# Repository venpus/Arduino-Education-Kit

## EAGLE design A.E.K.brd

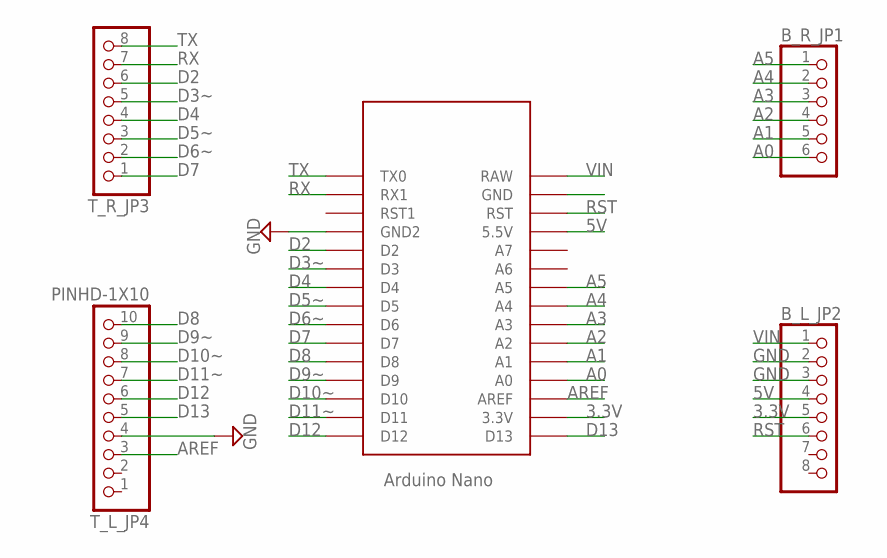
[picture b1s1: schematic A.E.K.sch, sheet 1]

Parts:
B_L_JP2: PINHD-1X8BIG; 1X08-BIG
B_R_JP1: PINHD-1X6B; 1X06-BIG
T_L_JP4: PINHD-1X10; 1X10-BIG
T_R_JP3: PINHD-1X8BIG; 1X08-BIG
U$1: NANO

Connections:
3.3V: B_L_JP2.5, U$1.3.3V
5V: B_L_JP2.4, U$1.5V (5.5V); also elsewhere on the board
A0: B_R_JP1.6, U$1.A0
A1: B_R_JP1.5, U$1.A1
A2: B_R_JP1.4, U$1.A2
A3: B_R_JP1.3, U$1.A3
A4: B_R_JP1.2, U$1.A4
A5: B_R_JP1.1, U$1.A5
AREF: T_L_JP4.3, U$1.AREF
D2: T_R_JP3.6, U$1.D2
D3~: T_R_JP3.5, U$1.D3
D4: T_R_JP3.4, U$1.D4
D5~: T_R_JP3.3, U$1.D5
D6~: T_R_JP3.2, U$1.D6
D7: T_R_JP3.1, U$1.D7
D8: T_L_JP4.10, U$1.D8
D9~: T_L_JP4.9, U$1.D9
D10~: T_L_JP4.8, U$1.D10
D11~: T_L_JP4.7, U$1.D11
D12: T_L_JP4.6, U$1.D12
D13: T_L_JP4.5, U$1.D13
GND: B_L_JP2.2, B_L_JP2.3, T_L_JP4.4, U$1.GND1 (GND2)
RST: B_L_JP2.6, U$1.RST
RX: T_R_JP3.7, U$1.RX1
TX: T_R_JP3.8, U$1.TX0
VIN: B_L_JP2.1, U$1.RAW

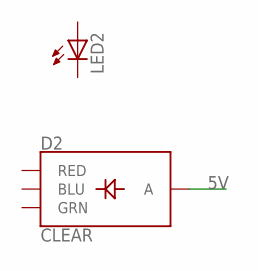
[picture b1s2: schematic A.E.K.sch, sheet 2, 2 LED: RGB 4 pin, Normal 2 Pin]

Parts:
D2: CLEAR; LED-RGB-THRU
LED2: LED5MM

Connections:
5V: D2.2 (A); also elsewhere on the board

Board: 2 copper layers, 7 parts (0 on the bottom side), 26 nets, no tracks yet.

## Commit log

2018-12-27 schemetics change
    remove unroute pin
2018-12-27 Add Dimension

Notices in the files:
parts and their libraries:
SparkFun-LED: Licensing: Creative Commons ShareAlike 4.0 International - https://creativecommons.org/licenses/by-sa/4.0
